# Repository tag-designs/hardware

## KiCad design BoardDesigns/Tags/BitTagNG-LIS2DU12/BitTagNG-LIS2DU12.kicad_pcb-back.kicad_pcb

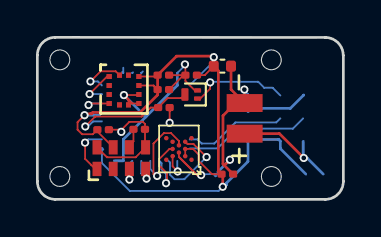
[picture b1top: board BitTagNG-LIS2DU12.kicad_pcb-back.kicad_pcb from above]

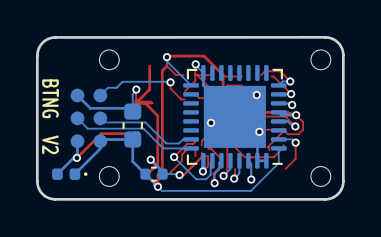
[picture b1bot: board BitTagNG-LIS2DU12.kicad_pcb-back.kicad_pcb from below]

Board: 2 copper layers, 17.0 x 9.0 mm, 22 parts (5 on the bottom side), 18 nets.

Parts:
C1, C2, C3, C501, C502, C503: 0.1uf; C_0201_0603Metric
C4, C404: 22uf; C_0402_1005Metric
C6: 47uf; C_0603_1608Metric
D401: D; D_0402_1005Metric
J201: CONN_02X04; tagpoints6
J301, J302, J303, J304: Conn_01x01; taghole1.1mm
J401: CONN_01X02; MS621
Q501: Q_NPN_BEC; SOT-883
R1: 10k; R_0201_0603Metric
U1: at25ex321D-UUN; adesto_wlcsp12
U3: LIS2DW12TR
U302: stm32l431kc; QFN-32-1EP_5x5mm_P0.5mm_EP3.45x3.45mm
U501: RV-3028-C7; RV-8803-C7

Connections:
/ACCEL_SCL: U3.1 (SCL/SPC), U302.7 (PA1)
/ACCEL_SDA: U3.4 (SDA/SDI/SDO), U302.6 (PA0)
/AT25_MISO: U1.D4 (SO), U302.27 (PB4)
/AT25_MOSI: U1.E3 (SI), U302.28 (PB5)
/AT25_SCK: U1.F2 (SCK), U302.26 (PB3)
/AT25_nCS: U1.B4 (nCS), U302.25 (PA15)
/SCL: U302.30 (PB7), U501.3 (SCL)
/SDA: U302.29 (PB6), U501.4 (SDA)
/WKUP4: U3.12 (INT1), U302.8 (PA2)
/clkout: U302.2 (PC14), U501.1 (CLKOUT)
GND: C1.2, C2.2, C3.2, C4.2, C6.2, C404.2, C501.2, C502.2, C503.2, J201.6, J401.2, Q501.2 (E), R1.2, U1.C3 (GND), U3.6 (GND), U3.7 (RES), U3.8 (GND), U302.16 (VSS), U302.31 (BOOT0), U302.32 (VSS), U302.33 (GND), U501.5 (GND), U501.8 (EVI)
unnamed: C502.1, Q501.3 (C), U302.4 (~NRST)
unnamed: R1.1, U501.6 (VBACK)
RST: J201.5, Q501.1 (B)
SWCLK: J201.4, U302.24 (PA14)
SWDIO: J201.3, U302.23 (PA13)
VBAT: D401.2 (A), J201.2, J401.1
VIN: C1.1, C2.1, C3.1, C4.1, C6.1, C404.1, C501.1, C503.1, D401.1 (K), J201.1, U1.B2 (VCC), U1.D2 (~RESET), U3.9 (VDD), U3.10 (VDDIO), U302.1 (VDD), U302.5 (VDDA/VREF+), U302.17 (VDD), U501.7 (VDD)

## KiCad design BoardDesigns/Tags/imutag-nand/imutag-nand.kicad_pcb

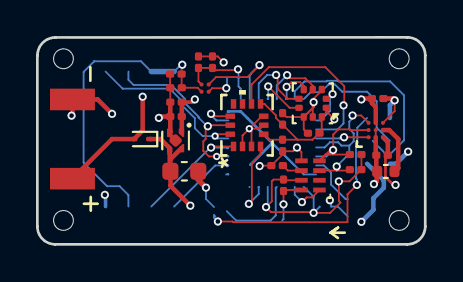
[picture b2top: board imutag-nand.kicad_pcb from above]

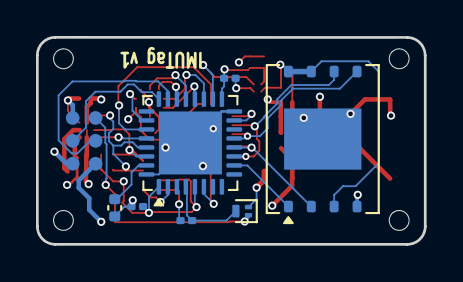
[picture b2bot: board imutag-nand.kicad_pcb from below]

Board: 4 copper layers, 21.5 x 11.5 mm, 37 parts (8 on the bottom side), 29 nets.

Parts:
C1, C2, C3, C5, C9, C11, C501, C502, C503, C505, C506, C507: 0.1uf; C_0201_0603Metric
C4: 2.2uf; C_0402_1005Metric
C7: 10uf; C_0603_1608Metric
C8, C10, C504: 1uf; C_0201_0603Metric
C12: 4.7uF; C_0402_1005Metric
D401: D; D_SOD-923
J201: CONN_02X04; tagpoints6
J301, J302, J303, J304: Conn_01x01; taghole1.1mm
J401: CONN_01X02; batterypads
Q501: Q_NPN_BEC; SOT-883
R1, R2, R3: 10k; R_0201_0603Metric
U1: TPS22916BYFPR; IC_TPS22916BYFPR
U2: BMM350; BGA9_BMM350_BOS
U3: LPS22HH; ST_HLGA-10_2x2mm_P0.5mm_LayoutBorder3x2y
U4: TPS7A02185PDQNR; Texas_X2SON-4_1x1mm_P0.65mm
U5: LSM6DSV16X; LGA14-L_2P59X3P1X0P5_STM
U6: GD5F1GQ5REYIGR; WSON-8-1EP_8x6mm_P1.27mm_EP3.4x4.3mm
U302: stm32U375; UFQFPN-32-1EP_5x5mm_P0.5mm_EP3.5x3.5mm
U501: RV-3028-C8

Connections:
+1V8: C1.1, C2.1, C3.1, C5.1, C8.1, C9.1, C10.1, C501.1, C503.1, C505.1, C506.1, C507.1, R2.1, R3.1, U1.A2 (VIN), U2.B3 (VDDIO), U2.C1 (VDD), U3.1 (Vdd_IO), U3.10 (VDD), U4.1 (OUT), U5.5 (VDD_IO), U5.8 (VDD), U302.1 (VDD), U302.5 (VDDA/VREF+), U302.17 (VDD), U501.7 (VDD)
/AT25_MISO: U5.1 (SDO/SA0), U6.2 (SO/SIO1), U302.12 (PA6)
/AT25_MOSI: U5.14 (SDA), U6.5 (SI/SIO0), U302.13 (PA7)
/AT25_SCK: U5.13 (SCL), U6.6 (SCLK), U302.11 (PA5)
/AT25_nCS: U6.1 (~CS), U302.10 (PA4)
/BMM_INT: U2.A1 (INT), U302.28 (PB5)
/FLASH_PWR: U1.B2 (ON), U302.18 (PA8)
/Flash 1V8: C11.1, C504.1, U1.A1 (VOUT), U6.3 (~WP/SIO2), U6.7 (~HOLD/SIO3), U6.8 (VCC)
/LPS_CK: U3.2 (SCL), U302.26 (PB3)
/LPS_CS: U3.6 (~CS), U302.19 (PA9)
/LPS_DRDY: U3.7 (INT_DRDY), U302.20 (PA10)
/LPS_MISO: U3.4 (SDA), U302.21 (PA11)
/LPS_MOSI: U3.5 (SA0), U302.22 (PA12)
/LSM_CS: U5.12 (CS), U302.15 (PB1)
/LSM_TRG: U5.9 (INT2), U302.27 (PB4)
/SCL: R2.2, U2.A3 (SCK), U302.29 (PB6), U501.3 (SCL)
/SDA: R3.2, U2.A2 (SDA), U302.30 (BOOT0-PB7), U501.4 (SDA)
/WKUP1: U5.4 (INT1), U302.6 (PA0)
/clkout: U302.2 (PC14), U501.1 (CLKOUT)
GND: C1.2, C2.2, C3.2, C4.2, C5.2, C7.2, C8.2, C9.2, C10.2, C11.2, C12.1, C501.2, C502.2, C503.2, C504.2, C505.2, C506.2, C507.2, J201.6, J401.2, Q501.2 (E), R1.2, U1.B1 (GND), U2.B1 (GND), U2.B2 (ADSEL), U2.C3 (BYPASS), U3.3 (GND), U3.8 (GND_IO), U3.9 (GND), U4.2 (GND), U4.5 (Pad), U5.2 (SDX), U5.3 (SCX), U5.6 (GND), U5.7 (GND), U6.4 (GND), U6.9 (EP), U302.16 (VSS), U302.32 (VSS), U302.33 (GND), U501.5 (GND), U501.8 (EVI)
unnamed: C502.1, Q501.3 (C), U302.4 (~NRST)
unnamed: C4.1, U2.C2 (CRST)
unnamed: C12.2, U302.31 (VCAP)
unnamed: R1.1, U501.6 (VBACK)
RST: J201.5, Q501.1 (B)
SWCLK: J201.4, U302.24 (PA14)
SWDIO: J201.3, U302.23 (PA13)
VBAT: D401.2 (A), J201.2, J401.1
VIN: C7.1, D401.1 (K), J201.1, U4.3 (EN), U4.4 (IN)

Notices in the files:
parts and their libraries:
Copyright 2016 Accelerated Designs. All rights reserved.
